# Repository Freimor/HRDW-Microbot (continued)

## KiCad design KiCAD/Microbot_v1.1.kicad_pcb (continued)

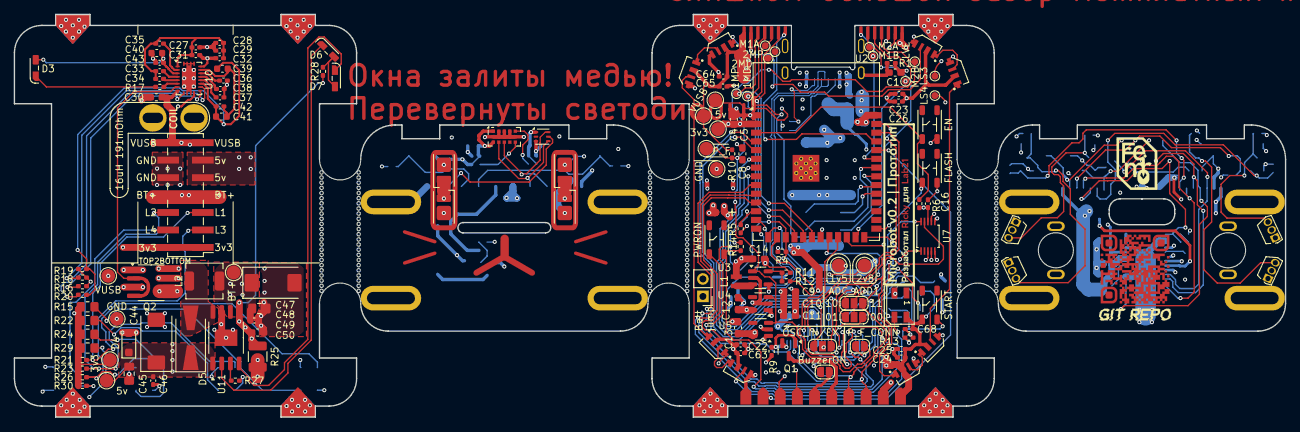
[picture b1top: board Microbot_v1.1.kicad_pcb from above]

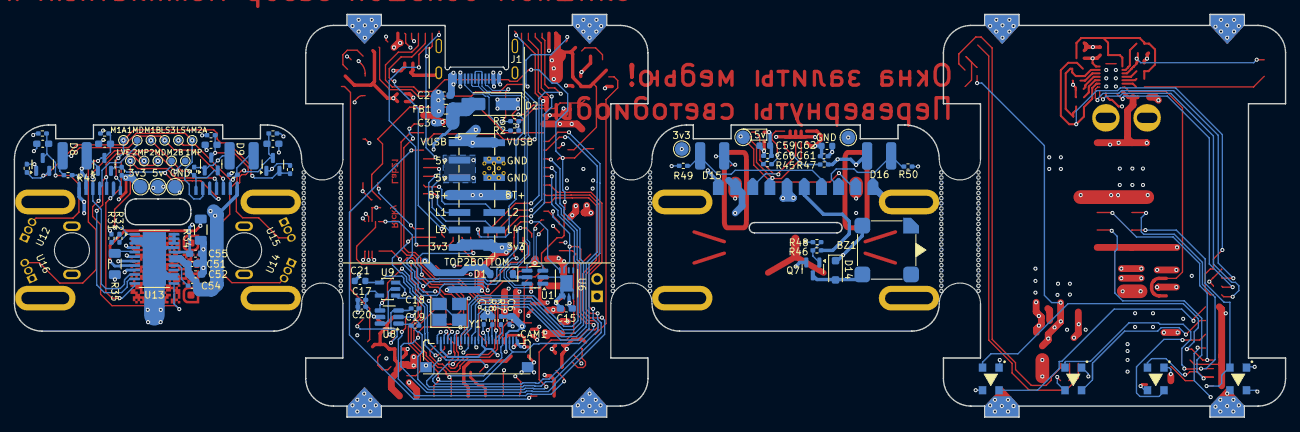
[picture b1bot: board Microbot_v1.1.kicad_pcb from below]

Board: 4 copper layers, 185.0 x 58.6 mm, 246 parts (92 on the bottom side), 123 nets.

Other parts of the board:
Ref**: Val**; Graphic

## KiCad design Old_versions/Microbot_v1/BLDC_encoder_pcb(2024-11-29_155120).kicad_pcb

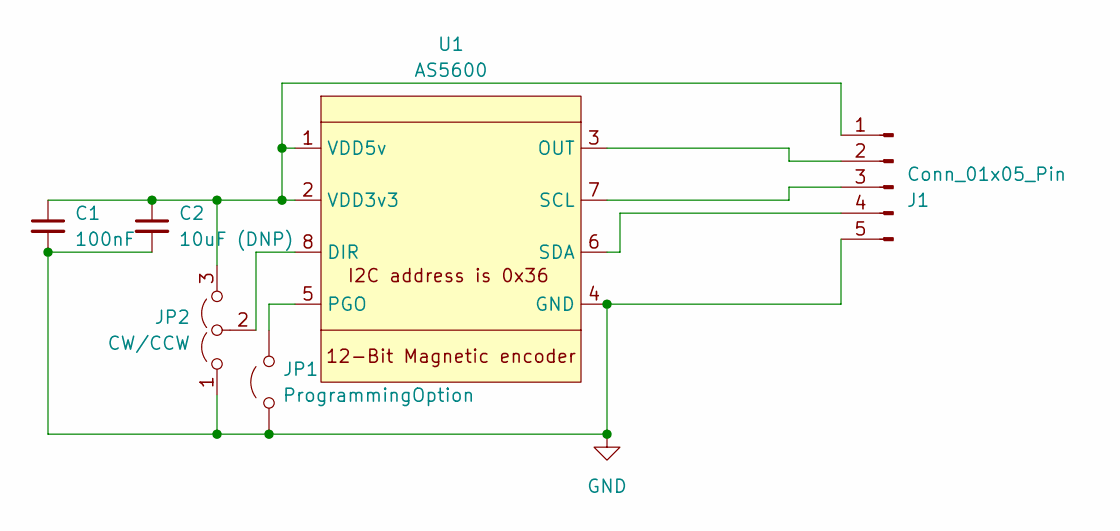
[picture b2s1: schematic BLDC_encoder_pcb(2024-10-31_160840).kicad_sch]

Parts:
C1: 100nF; C_0402_1005Metric_Pad0.74x0.62mm_HandSolder
C2: 10uF (DNP); C_0603_1608Metric_Pad1.08x0.95mm_HandSolder
J1: Conn_01x05_Pin; Microbot_BLDC_encoder
JP1: ProgrammingOption; SolderJumper-2_P1.3mm_Open_RoundedPad1.0x1.5mm
JP2: CW/CCW; SolderJumper-3_P1.3mm_Open_RoundedPad1.0x1.5mm_NumberLabels
U1: AS5600; SOIC-8_3.9x4.9mm_P1.27mm

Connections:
GND: C1.2, C2.2, J1.5, JP1.1 (A), JP2.1 (A), U1.4 (GND)
unnamed: C1.1, C2.1, J1.1, JP2.3 (B), U1.1 (VDD5v), U1.2 (VDD3v3)
unnamed: J1.2, U1.3 (OUT)
unnamed: J1.3, U1.7 (SCL)
unnamed: J1.4, U1.6 (SDA)
unnamed: JP1.2 (B), U1.5 (PGO)
unnamed: JP2.2 (C), U1.8 (DIR)

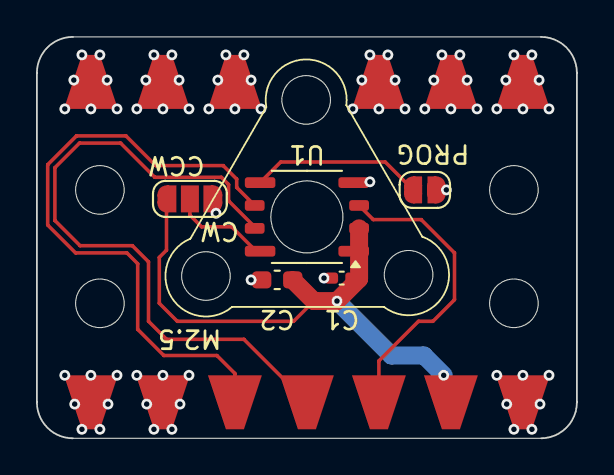
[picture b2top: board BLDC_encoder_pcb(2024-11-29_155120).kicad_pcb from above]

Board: 2 copper layers, 30.0 x 22.3 mm, 6 parts (0 on the bottom side), 7 nets.

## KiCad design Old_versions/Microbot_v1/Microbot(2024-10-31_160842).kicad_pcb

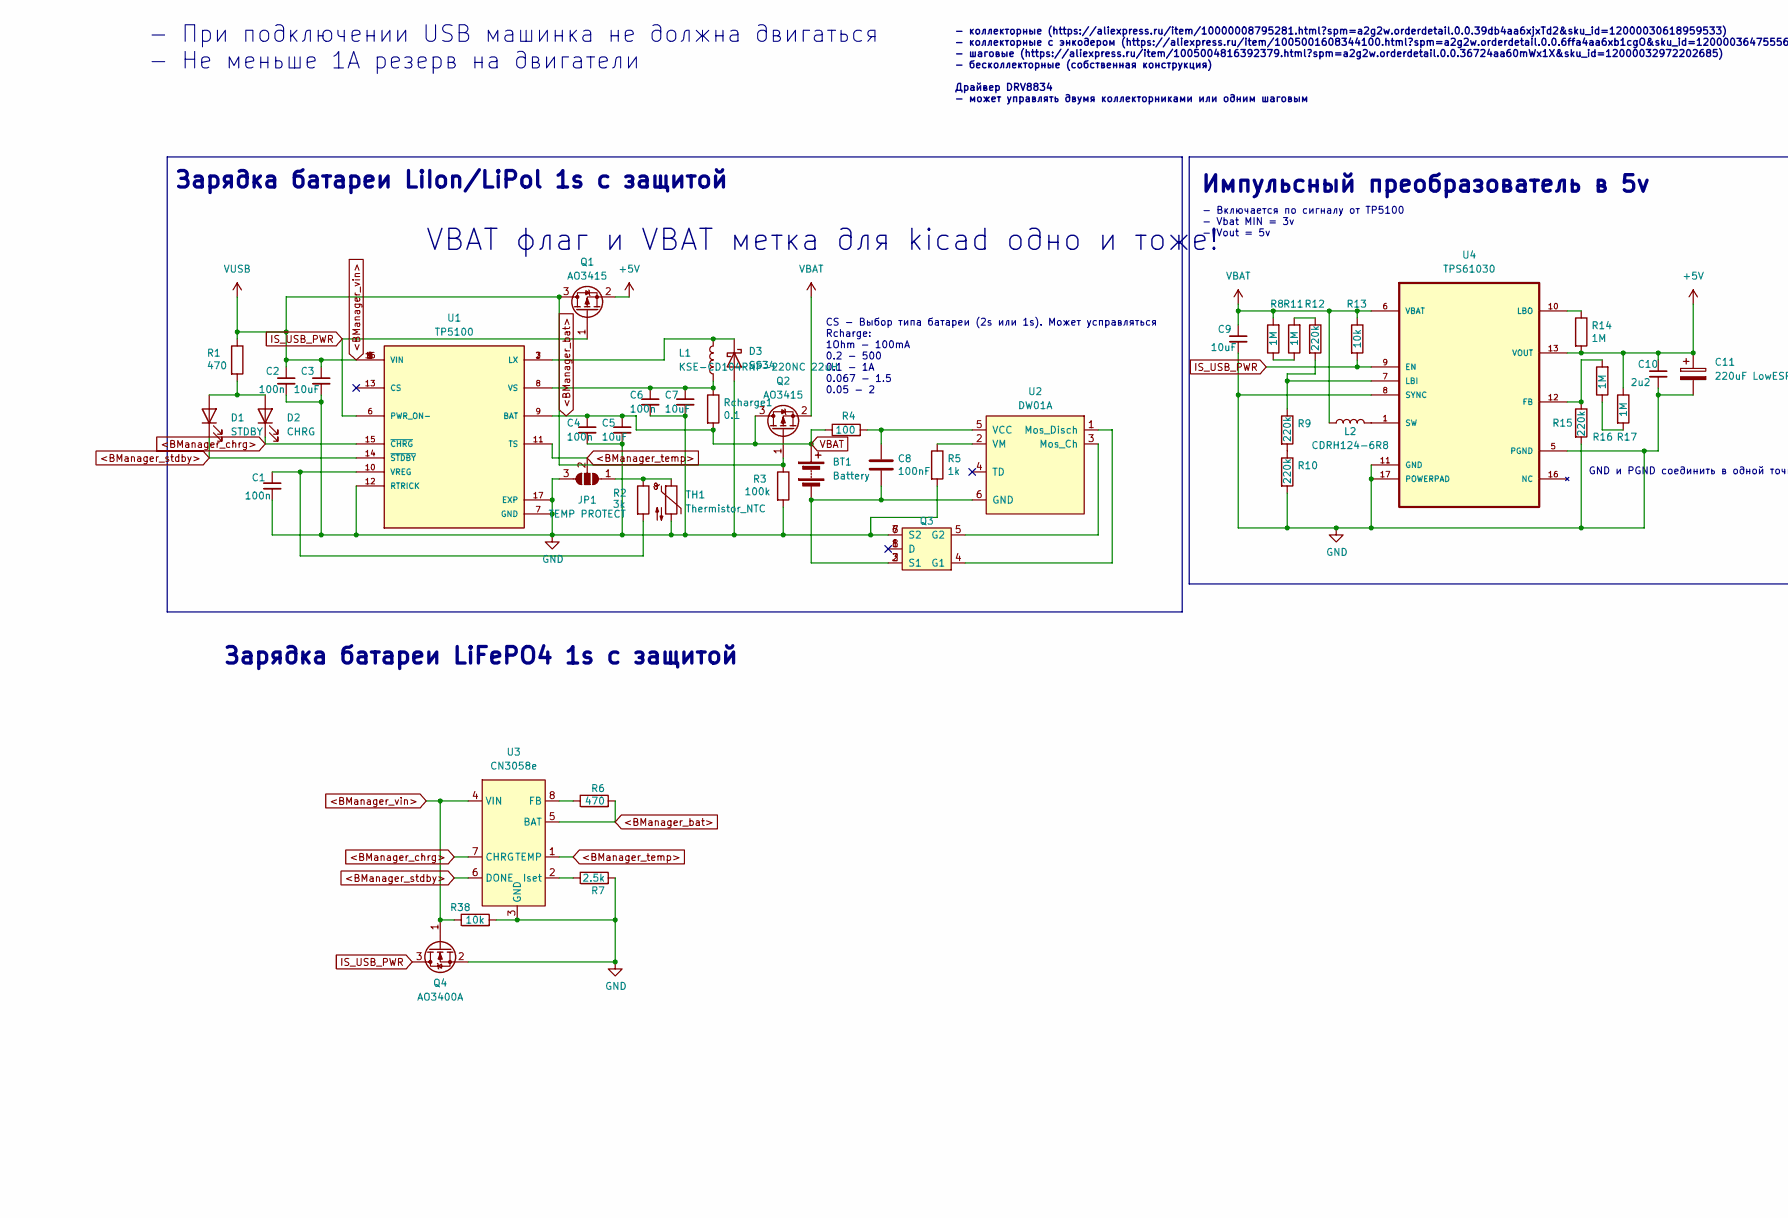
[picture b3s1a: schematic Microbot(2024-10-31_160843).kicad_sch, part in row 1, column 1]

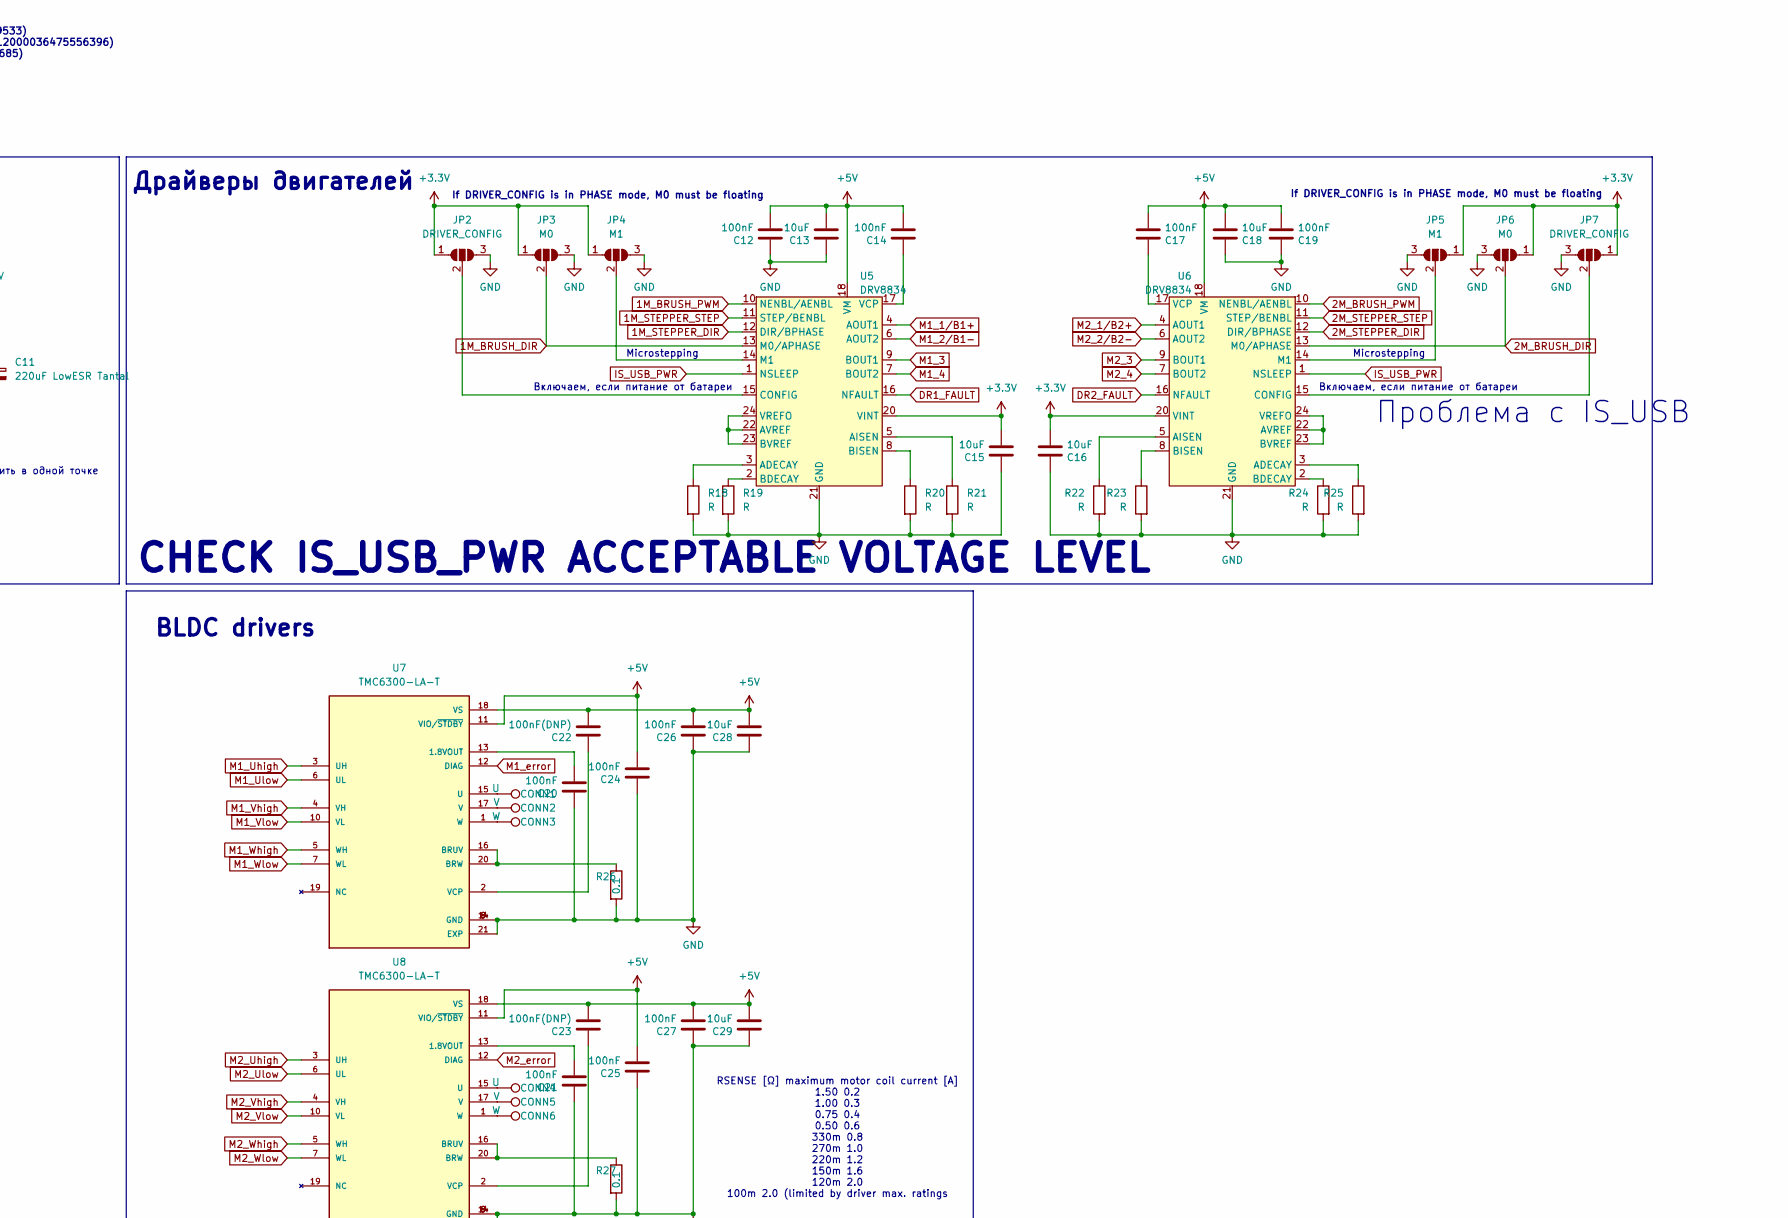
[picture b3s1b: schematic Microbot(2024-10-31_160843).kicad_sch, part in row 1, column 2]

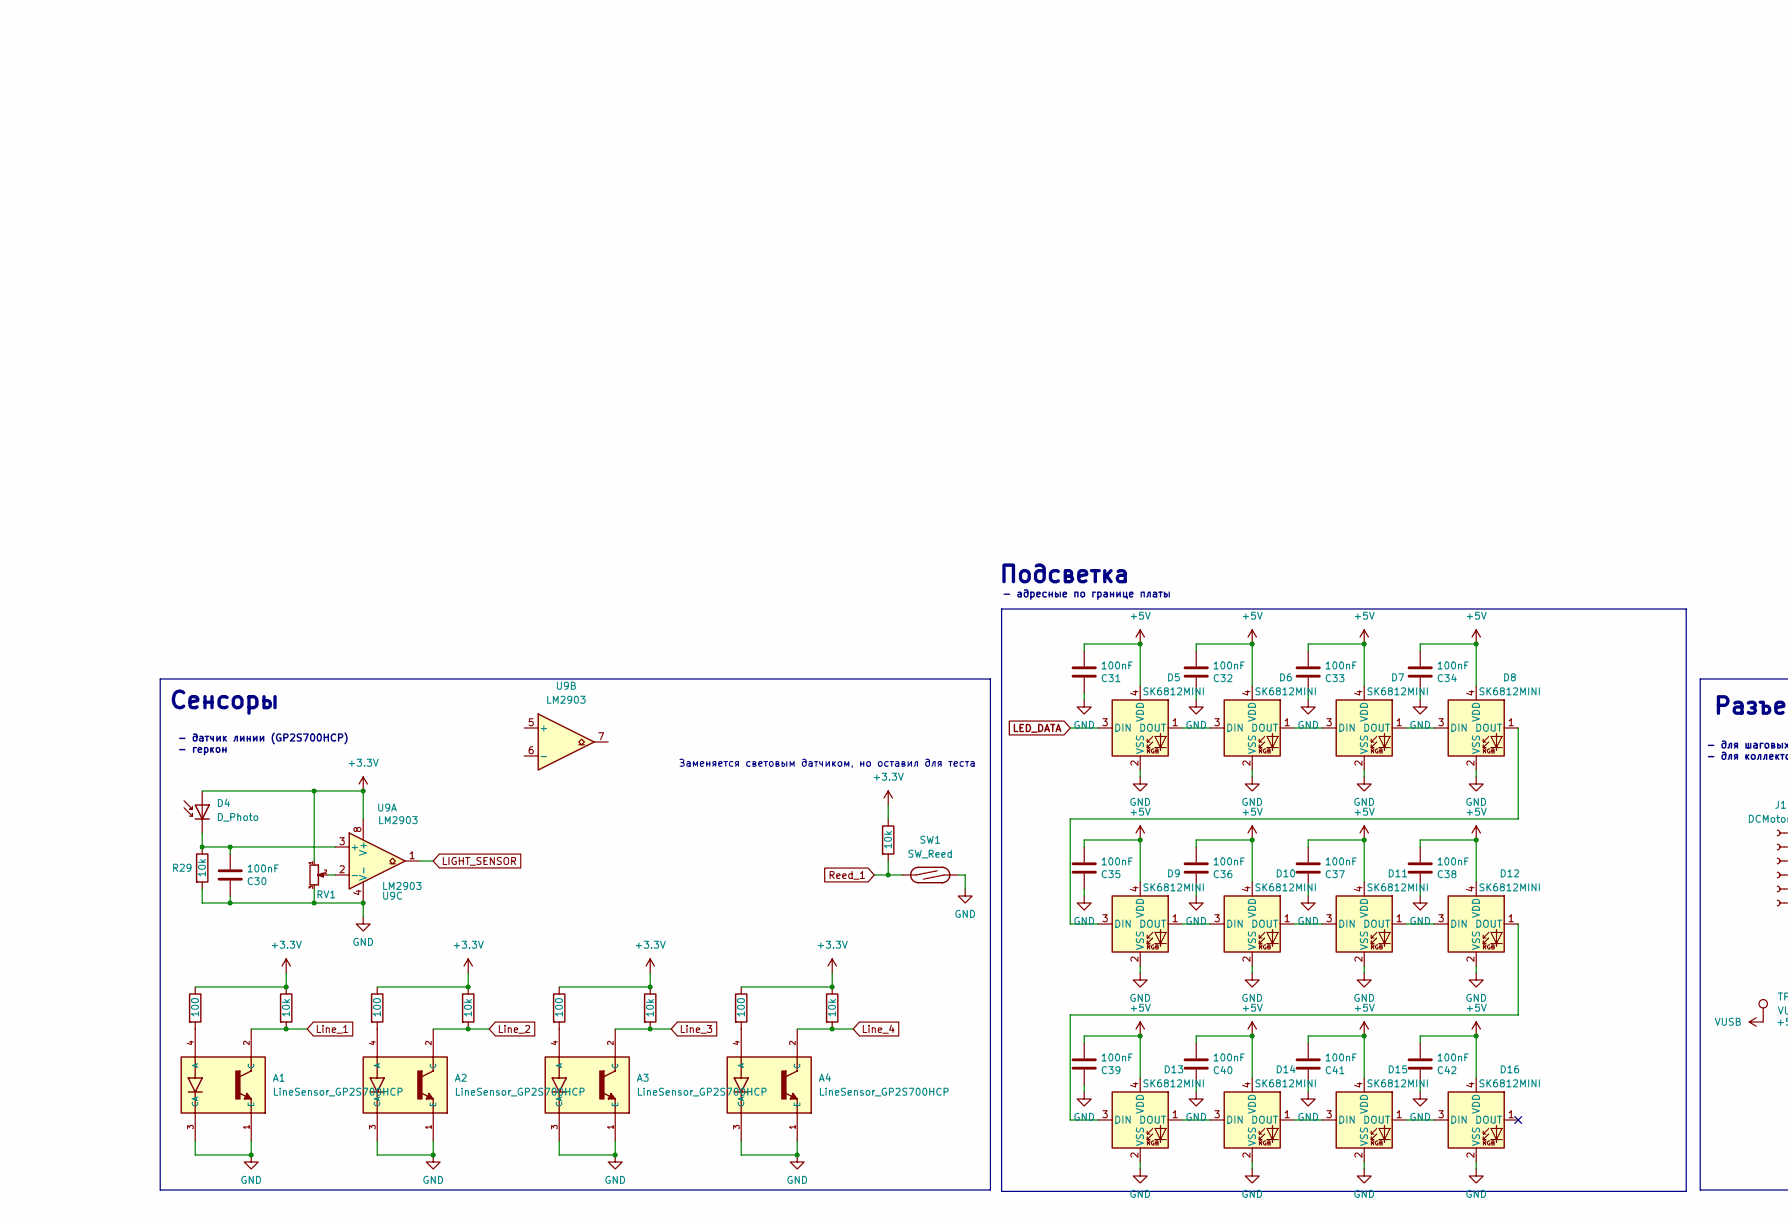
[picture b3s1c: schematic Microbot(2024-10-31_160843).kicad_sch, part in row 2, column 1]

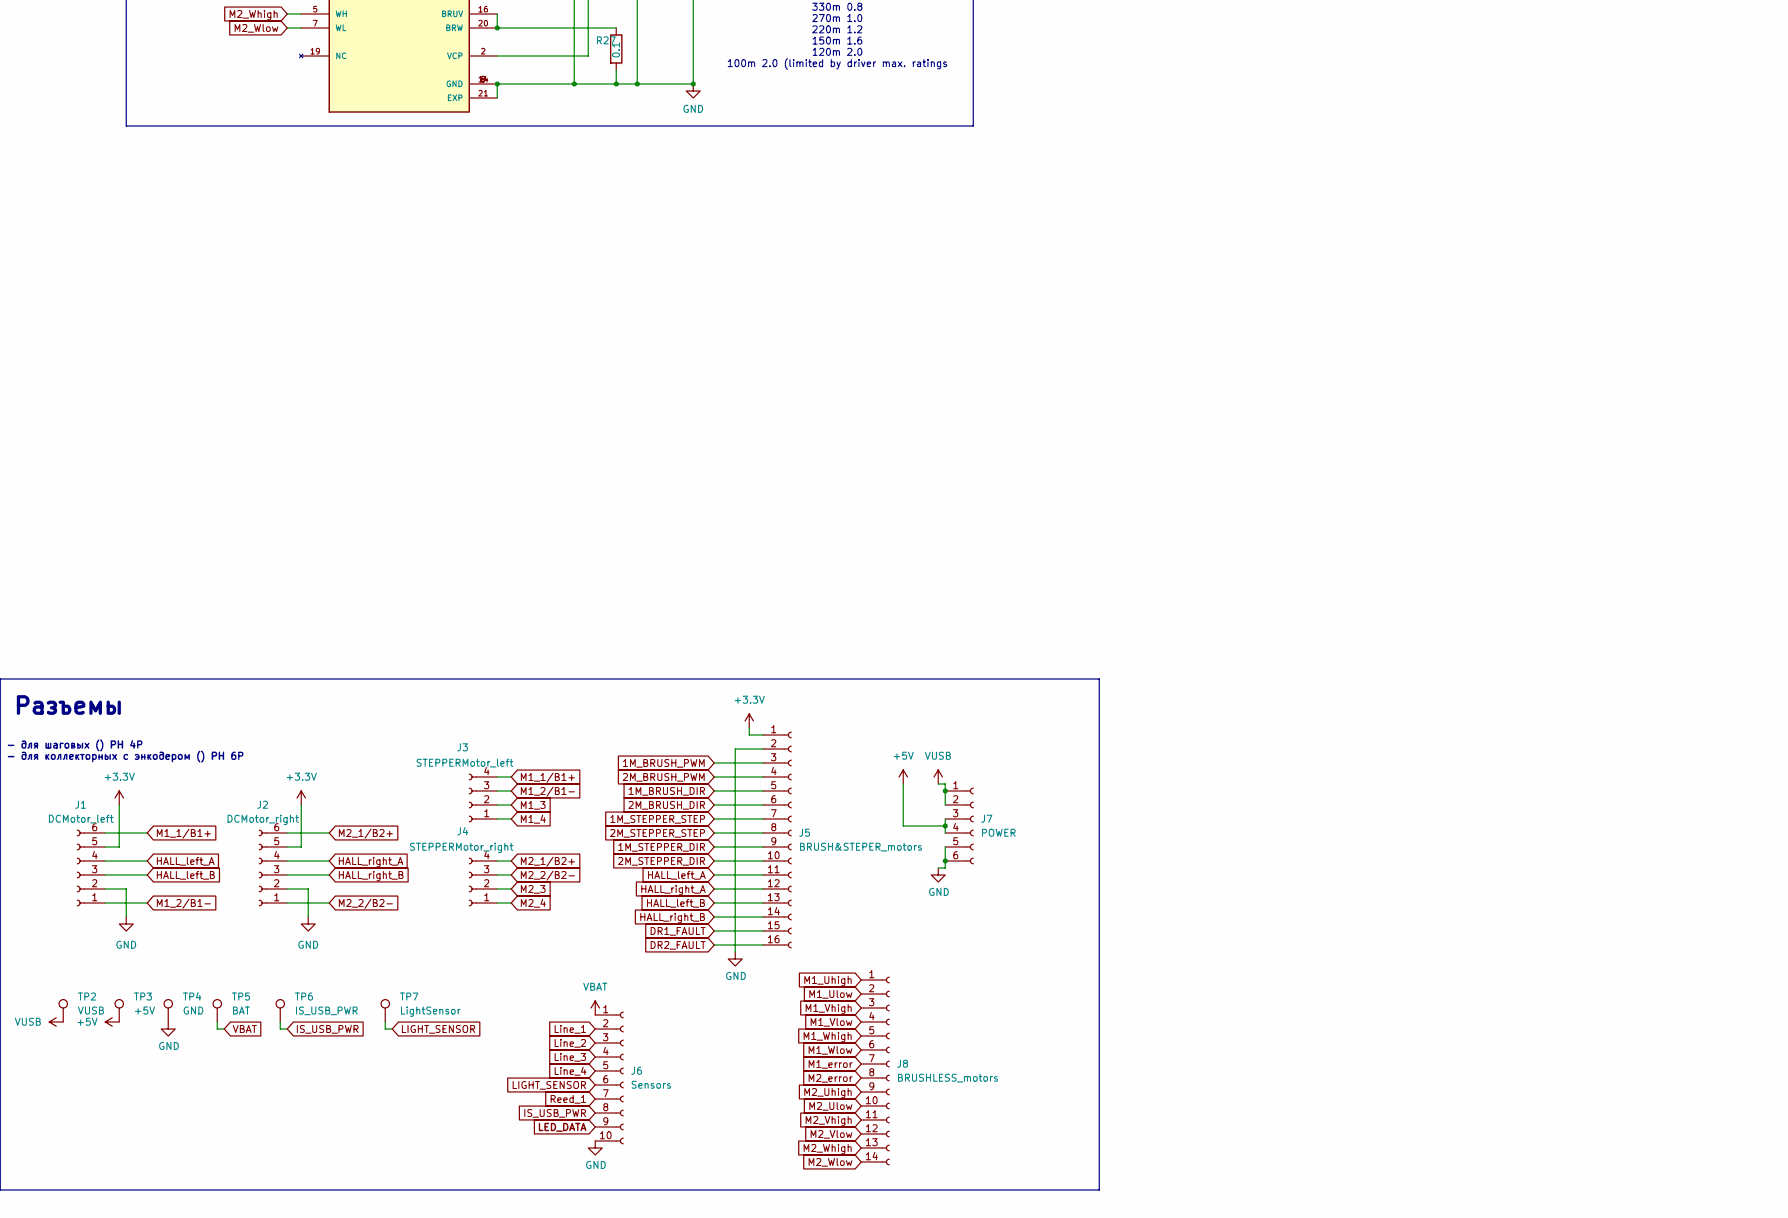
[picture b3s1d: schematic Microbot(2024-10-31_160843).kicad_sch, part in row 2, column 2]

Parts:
A1, A2, A3, A4: LineSensor_GP2S700HCP; GP2S700HCP; PARTREV Oct. 3. 2005
BT1: Battery; Conn_BAT_18650_LowProfile
C1, C2, C4, C6: 100n; C_0402_1005Metric_Pad0.74x0.62mm_HandSolder
C3, C5, C7, C9, C13, C15, C16, C18, C28, C29: 10uF; C_0603_1608Metric_Pad1.08x0.95mm_HandSolder
C8, C12, C14, C17, C19, C20, C21, C24, C25, C26, C27, C30, C31, C32, C33, C34, C35, C36, C37, C38, C39, C40, C41, C42: 100nF; C_0402_1005Metric_Pad0.74x0.62mm_HandSolder
C10: 2u2; C_0603_1608Metric_Pad1.08x0.95mm_HandSolder
C11: 220uF LowESR Tantal; CP_EIA-7343-31_Kemet-D
C22, C23: 100nF(DNP); C_0402_1005Metric_Pad0.74x0.62mm_HandSolder
CONN1, CONN4: U; TestPoint_Pad_D1.5mm
CONN2, CONN5: V; TestPoint_Pad_D1.5mm
CONN3, CONN6: W; TestPoint_Pad_D1.5mm
D1: STDBY; LED_0603_1608Metric
D2: CHRG; LED_0603_1608Metric
D3: SS34; D_SMA-SMB_Universal_Handsoldering
D4: D_Photo; R_LDR_5.1x4.3mm_P3.4mm_Vertical
D5, D6, D7, D8, D9, D10, D11, D12, D13, D14, D15, D16: SK6812MINI; LED_SK6812MINI_PLCC4_3.5x3.5mm_P1.75mm
J1: DCMotor_left; JST_ZH_B6B-ZR-SM4-TF_1x06-1MP_P1.50mm_Vertical
J2: DCMotor_right; JST_ZH_B6B-ZR-SM4-TF_1x06-1MP_P1.50mm_Vertical
J3: STEPPERMotor_left; JST_PH_S4B-PH-SM4-TB_1x04-1MP_P2.00mm_Horizontal
J4: STEPPERMotor_right; JST_PH_S4B-PH-SM4-TB_1x04-1MP_P2.00mm_Horizontal
J5: BRUSH&STEPER_motors; PinHeader_2x08_P2.54mm_Vertical_SMD
J6: Sensors; PinHeader_2x05_P2.54mm_Vertical_SMD
J7: POWER; PinHeader_2x03_P2.54mm_Vertical_SMD
J8: BRUSHLESS_motors; PinHeader_2x07_P2.54mm_Vertical_SMD
JP1: TEMP PROTECT; SolderJumper-3_P1.3mm_Open_RoundedPad1.0x1.5mm
JP2, JP7: DRIVER_CONFIG; SolderJumper-3_P1.3mm_Open_RoundedPad1.0x1.5mm
JP3, JP6: M0; SolderJumper-3_P1.3mm_Open_RoundedPad1.0x1.5mm
JP4, JP5: M1; SolderJumper-3_P1.3mm_Open_RoundedPad1.0x1.5mm
L1: KSE-CD104RNP-220NC 22uH; L_10.4x10.4_H4.8
L2: CDRH124-6R8; L_12x12mm_H4.5mm
Q1, Q2: AO3415; SOT-23
Q3: 8205(Dual_Mosfet); SOT-23-6
Q4: AO3400A; SOT-23
R1, R6: 470; R_0402_1005Metric_Pad0.72x0.64mm_HandSolder
R2: 3k; R_0603_1608Metric
R3: 100k; R_0402_1005Metric_Pad0.72x0.64mm_HandSolder
R4: 100; R_0402_1005Metric_Pad0.72x0.64mm_HandSolder
R5: 1k; R_0402_1005Metric_Pad0.72x0.64mm_HandSolder
R7: 2.5k; R_0805_2012Metric_Pad1.20x1.40mm_HandSolder
R8, R11, R14, R16, R17: 1M; R_0402_1005Metric_Pad0.72x0.64mm_HandSolder
R9, R10, R12, R15: 220k; R_0402_1005Metric_Pad0.72x0.64mm_HandSolder
R13, R29, R30, R32, R34, R36, R37, R38: 10k; R_0402_1005Metric_Pad0.72x0.64mm_HandSolder
R18, R19, R20, R21, R22, R23, R24, R25: R; R_0805_2012Metric_Pad1.20x1.40mm_HandSolder
R26, R27: 0.1; R_0805_2012Metric_Pad1.20x1.40mm_HandSolder
R28, R31, R33, R35: 100; R_0805_2012Metric_Pad1.20x1.40mm_HandSolder
RV1: R_Potentiometer_Small; POT_SMD_3x3mm
Rcharge1: 0.1; R_1206_3216Metric_Pad1.30x1.75mm_HandSolder
SW1: SW_Reed; Reed_MKA10110
TH1: Thermistor_NTC; R_Axial_DIN0204_L3.6mm_D1.6mm_P7.62mm_Horizontal
TP2: VUSB; TestPoint_Pad_D2.0mm
TP3: +5V; TestPoint_Pad_D2.0mm
TP4: GND; TestPoint_Pad_D2.0mm
TP5: BAT; TestPoint_Pad_D2.0mm
TP6: IS_USB_PWR; TestPoint_Pad_D2.0mm
TP7: LightSensor; TestPoint_Pad_D2.0mm
U1: TP5100; QFN-16-1EP_4x4mm_P0.65mm_EP2.1x2.1mm; PARTREV 2.3
U2: DW01A; SOT-23-6_Handsoldering
U3: CN3058e; SOP-8_3.9x4.9mm_P1.27mm
U4: TPS61030; HTSSOP-16-1EP_4.4x5mm_P0.65mm_EP3x3mm; MPN TPS61030
U5, U6: DRV8834; HTSSOP-24-1EP_4.4x7.8mm_P0.65mm_EP3.4x7.8mm_Mask2.4x2.98mm
U7, U8: TMC6300-LA-T; TMC6300; PARTREV 1.08
U9: LM2903; SOIC-8_3.9x4.9mm_P1.27mm

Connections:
1M_BRUSH_DIR: J5.5, JP3.2 (C), U5.13 (M0/APHASE)
1M_BRUSH_PWM: J5.3, U5.10 (NENBL/AENBL)
1M_STEPPER_DIR: J5.9, U5.12 (DIR/BPHASE)
1M_STEPPER_STEP: J5.7, U5.11 (STEP/BENBL)
2M_BRUSH_DIR: J5.6, JP6.2 (C), U6.13 (M0/APHASE)
2M_BRUSH_PWM: J5.4, U6.10 (NENBL/AENBL)
2M_STEPPER_DIR: J5.10, U6.12 (DIR/BPHASE)
2M_STEPPER_STEP: J5.8, U6.11 (STEP/BENBL)
+3.3V: C15.2, C16.2, D4.2 (A), J1.5, J2.5, J5.1, JP2.1 (A), JP3.1 (A), JP4.1 (A), JP5.1 (A), JP6.1 (A), JP7.1 (A), R28.1, R30.1, R31.1, R32.1, R33.1, R34.1, R35.1, R36.1, R37.1, RV1.1, U5.20 (VINT), U6.20 (VINT), U9.8 (V+)
+5V: C10.1, C11.1, C12.2, C13.2, C14.2, C17.2, C18.2, C19.2, C22.2, C23.2, C24.2, C25.2, C26.2, C27.2, C28.2, C29.2, C31.2, C32.2, C33.2, C34.2, C35.2, C36.2, C37.2, C38.2, C39.2, C40.2, C41.2, C42.2, D5.4 (VDD), D6.4 (VDD), D7.4 (VDD), D8.4 (VDD), D9.4 (VDD), D10.4 (VDD), D11.4 (VDD), D12.4 (VDD), D13.4 (VDD), D14.4 (VDD), D15.4 (VDD), D16.4 (VDD), J7.3, J7.4, Q1.2 (S), R14.2, R17.1, TP3.1, U4.13 (VOUT), U4.14 (VOUT_2), U4.15 (VOUT_3), U5.18 (VM), U5.19 (VM), U6.18 (VM), U6.19 (VM), U7.11 (VIO/~STDBY), U7.18 (VS), U8.11 (VIO/~STDBY), U8.18 (VS)
<BManager_bat>: BT1.1 (+), C4.1, C5.1, C9.1, J6.1, L2.1, Q2.2 (S), Q2.3 (D), R4.1, R6.2, R8.2, R13.1, Rcharge1.2, TP5.1, U1.9 (BAT), U3.5 (BAT), U4.6 (VBAT)
<BManager_chrg>: D2.1 (K), U1.15 (~CHRG), U3.7 (CHRG)
<BManager_stdby>: D1.1 (K), U1.14 (~STDBY), U3.6 (DONE)
<BManager_temp>: JP1.2 (C), U1.11 (TS), U3.1 (TEMP)
<BManager_vin>: C2.1, C3.1, J7.1, J7.2, Q1.3 (D), Q2.1 (G), Q4.1 (G), R1.1, R3.1, R38.1, TP2.1, U1.1 (VIN), U1.4 (VIN), U1.5 (VIN), U1.16 (VIN), U3.4 (VIN)
DR1_FAULT: J5.15, U5.16 (NFAULT)
DR2_FAULT: J5.16, U6.16 (NFAULT)
GND: A1.1 (E), A1.3 (CA), A2.1 (E), A2.3 (CA), A3.1 (E), A3.3 (CA), A4.1 (E), A4.3 (CA), C1.2, C2.2, C3.2, C4.2, C5.2, C6.2, C7.2, C9.2, C10.2, C11.2, C12.1, C13.1, C15.1, C16.1, C18.1, C19.1, C20.1, C21.1, C24.1, C25.1, C26.1, C27.1, C28.1, C29.1, C30.1, C31.1, C32.1, C33.1, C34.1, C35.1, C36.1, C37.1, C38.1, C39.1, C40.1, C41.1, C42.1, D3.2 (A), D5.2 (VSS), D6.2 (VSS), D7.2 (VSS), D8.2 (VSS), D9.2 (VSS), D10.2 (VSS), D11.2 (VSS), D12.2 (VSS), D13.2 (VSS), D14.2 (VSS), D15.2 (VSS), D16.2 (VSS), J1.2, J2.2, J5.2, J6.10, J7.5, J7.6, JP1.3 (B), JP2.3 (B), JP3.3 (B), JP4.3 (B), JP5.3 (B), JP6.3 (B), JP7.3 (B), Q3.6 (S2), Q3.7 (S2), Q4.2 (S), R3.2, R5.2, R7.2, R10.2, R15.2, R18.2, R19.2, R20.2, R21.2, R22.2, R23.2, R24.2, R25.2, R26.2, R27.2, R29.2, R38.2, RV1.3, SW1.2, TH1.2, TP4.1, U1.7 (GND), U1.12 (RTRICK), U1.17 (EXP), U3.3 (GND), U4.3 (PGND_2), U4.4 (PGND_3), U4.5 (PGND), U4.8 (SYNC), U4.11 (GND), U4.17 (POWERPAD), U5.21 (GND), U6.21 (GND), U7.8 (GND), U7.9 (GND), U7.14 (GND), U7.21 (EXP), U8.8 (GND), U8.9 (GND), U8.14 (GND), U8.21 (EXP), U9.4 (V-)
HALL_left_A: J1.4, J5.11
HALL_left_B: J1.3, J5.13
HALL_right_A: J2.4, J5.12
HALL_right_B: J2.3, J5.14
IS_USB_PWR: J6.8, Q1.1 (G), Q4.3 (D), R13.2, TP6.1, U1.6 (PWR_ON-), U4.9 (EN), U5.1 (NSLEEP), U6.1 (NSLEEP)
LED_DATA: D5.3 (DIN), J6.9
Line_1: A1.2 (C), J6.2, R30.2
Line_2: A2.2 (C), J6.3, R32.2
Line_3: A3.2 (C), J6.4, R34.2
Line_4: A4.2 (C), J6.5, R36.2
M1_1/B1+: J1.6, J3.4, U5.4 (AOUT1)
M1_2/B1-: J1.1, J3.3, U5.6 (AOUT2)
M1_3: J3.2, U5.9 (BOUT1)
M1_4: J3.1, U5.7 (BOUT2)
M1_Uhigh: J8.1, U7.3 (UH)
M1_Ulow: J8.2, U7.6 (UL)
M1_Vhigh: J8.3, U7.4 (VH)
M1_Vlow: J8.4, U7.10 (VL)
M1_Whigh: J8.5, U7.5 (WH)
M1_Wlow: J8.6, U7.7 (WL)
M1_error: J8.7, U7.12 (DIAG)
M2_1/B2+: J2.6, J4.4, U6.4 (AOUT1)
M2_2/B2-: J2.1, J4.3, U6.6 (AOUT2)
M2_3: J4.2, U6.9 (BOUT1)
M2_4: J4.1, U6.7 (BOUT2)
M2_Uhigh: J8.9, U8.3 (UH)
M2_Ulow: J8.10, U8.6 (UL)
M2_Vhigh: J8.11, U8.4 (VH)
M2_Vlow: J8.12, U8.10 (VL)
M2_Whigh: J8.13, U8.5 (WH)
M2_Wlow: J8.14, U8.7 (WL)
M2_error: J8.8, U8.12 (DIAG)
unnamed: A1.4 (A), R28.2
unnamed: A2.4 (A), R31.2
unnamed: A3.4 (A), R33.2
unnamed: A4.4 (A), R35.2
unnamed: BT1.2 (-), C8.2, Q3.2 (S1), Q3.3 (S1), U2.6 (GND)
unnamed: D1.2 (A), D2.2 (A), R1.2
unnamed: D3.1 (K), L1.2, U1.2 (LX), U1.3 (LX)
unnamed: C30.2, D4.1 (K), R29.1, U9.3 (+)
unnamed: D5.1 (DOUT), D6.3 (DIN)
unnamed: D6.1 (DOUT), D7.3 (DIN)
unnamed: D7.1 (DOUT), D8.3 (DIN)
unnamed: D8.1 (DOUT), D9.3 (DIN)
unnamed: D9.1 (DOUT), D10.3 (DIN)
unnamed: D10.1 (DOUT), D11.3 (DIN)
unnamed: D11.1 (DOUT), D12.3 (DIN)
unnamed: D12.1 (DOUT), D13.3 (DIN)
unnamed: D13.1 (DOUT), D14.3 (DIN)
unnamed: D14.1 (DOUT), D15.3 (DIN)
unnamed: D15.1 (DOUT), D16.3 (DIN)
unnamed: JP1.1 (A), R2.1, TH1.1
unnamed: JP2.2 (C), U5.15 (CONFIG)
unnamed: JP4.2 (C), U5.14 (M1)
unnamed: JP5.2 (C), U6.14 (M1)
unnamed: JP7.2 (C), U6.15 (CONFIG)
unnamed: L2.2, U4.1 (SW), U4.2 (SW)
unnamed: Q3.4 (G1), U2.1 (Mos_Disch)
unnamed: Q3.5 (G2), U2.3 (Mos_Ch)
unnamed: R9.2, R10.1
unnamed: R8.1, R11.1
unnamed: R11.2, R12.1
unnamed: R16.1, R17.2
unnamed: C1.1, R2.2, U1.10 (VREG)
unnamed: C6.1, C7.1, L1.1, Rcharge1.1, U1.8 (VS)
unnamed: C8.1, R4.2, U2.5 (VCC)
unnamed: R5.1, U2.2 (VM)
unnamed: R6.1, U3.8 (FB)
unnamed: R7.1, U3.2 (Iset)
unnamed: R15.1, R16.2, U4.12 (FB)
unnamed: R9.1, R12.2, U4.7 (LBI)
unnamed: R14.1, U4.10 (LBO)
unnamed: R18.1, U5.3 (ADECAY)
unnamed: R21.1, U5.5 (AISEN)
unnamed: U5.22 (AVREF), U5.23 (BVREF), U5.24 (VREFO)
unnamed: R19.1, U5.2 (BDECAY)
unnamed: R20.1, U5.8 (BISEN)
unnamed: C14.1, U5.17 (VCP)
unnamed: R25.1, U6.3 (ADECAY)
unnamed: R22.1, U6.5 (AISEN)
unnamed: U6.22 (AVREF), U6.23 (BVREF), U6.24 (VREFO)
unnamed: R24.1, U6.2 (BDECAY)
unnamed: R23.1, U6.8 (BISEN)
unnamed: C17.1, U6.17 (VCP)
unnamed: C20.2, U7.13 (1.8VOUT)
unnamed: R26.1, U7.16 (BRUV), U7.20 (BRW)
unnamed: CONN1.1, U7.15 (U)
unnamed: CONN2.1, U7.17 (V)
unnamed: C22.1, U7.2 (VCP)
unnamed: CONN3.1, U7.1 (W)
unnamed: C21.2, U8.13 (1.8VOUT)
unnamed: R27.1, U8.16 (BRUV), U8.20 (BRW)
unnamed: CONN4.1, U8.15 (U)
unnamed: CONN5.1, U8.17 (V)
unnamed: C23.1, U8.2 (VCP)
unnamed: CONN6.1, U8.1 (W)
unnamed: RV1.2, U9.2 (-)

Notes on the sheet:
Импульсный преобразователь в 5v
Включаем, если питание от батареи
- для шаговых () PH 4P - для коллекторных с энкодером () PH 6P
Заменяется световым датчиком, но оставил для теста
Драйверы двигателей
- При подключении USB машинка не должна двигаться - Не меньше 1А резерв на двигатели
Разъемы
Зарядка батареи LiFePO4 1s с защитой
- Включается по сигналу от TP5100 - Vbat MIN = 3v - Vout = 5v
Проблема с IS_USB
If DRIVER_CONFIG is in PHASE mode, M0 must be floating
- адресные по границе платы
Подсветка
Зарядка батареи LiIon/LiPol 1s с защитой
- коллекторные (https://aliexpress.ru/item/10000008795281.html?spm=a2g2w.orderdetail.0.0.39db4aa6xjxTd2&sku_id=12000030618959533) - коллекторные с энкодером (https://aliexpress.ru/item/1005001608344100.html?spm=a2g2w.orderdetail.0.0.6ffa4aa6xb1cgO&sku_id=12000036475556396) - шаговые (https://aliexp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
CHECK IS_USB_PWR ACCEPTABLE VOLTAGE LEVEL
- датчик линии (GP2S700HCP) - геркон
Сенсоры
Microstepping
VBAT флаг и VBAT метка для kicad одно и тоже!
CS - Выбор типа батареи (2s или 1s). Может усправляться Rcharge: 1Ohm - 100mA 0.2 - 500 0.1 - 1A 0.067 - 1.5 0.05 - 2
GND и PGND соединить в одной точке
RSENSE [Ω] maximum motor coil current [A] 1.50 0.2 1.00 0.3 0.75 0.4 0.50 0.6 330m 0.8 270m 1.0 220m 1.2 150m 1.6 120m 2.0 100m 2.0 (limited by driver max. ratings
BLDC drivers

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
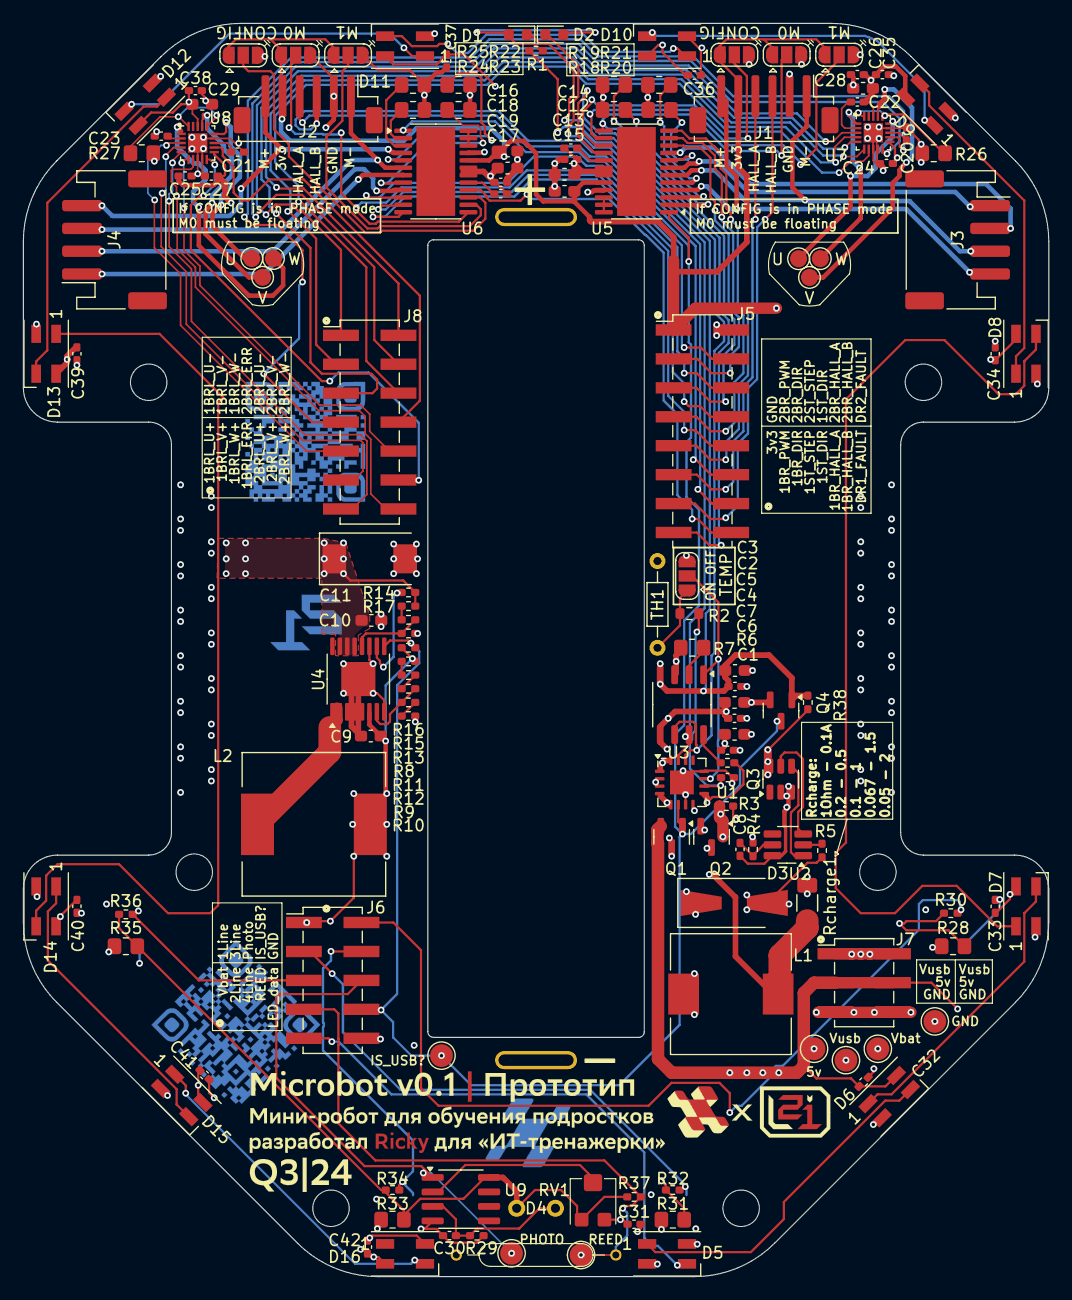
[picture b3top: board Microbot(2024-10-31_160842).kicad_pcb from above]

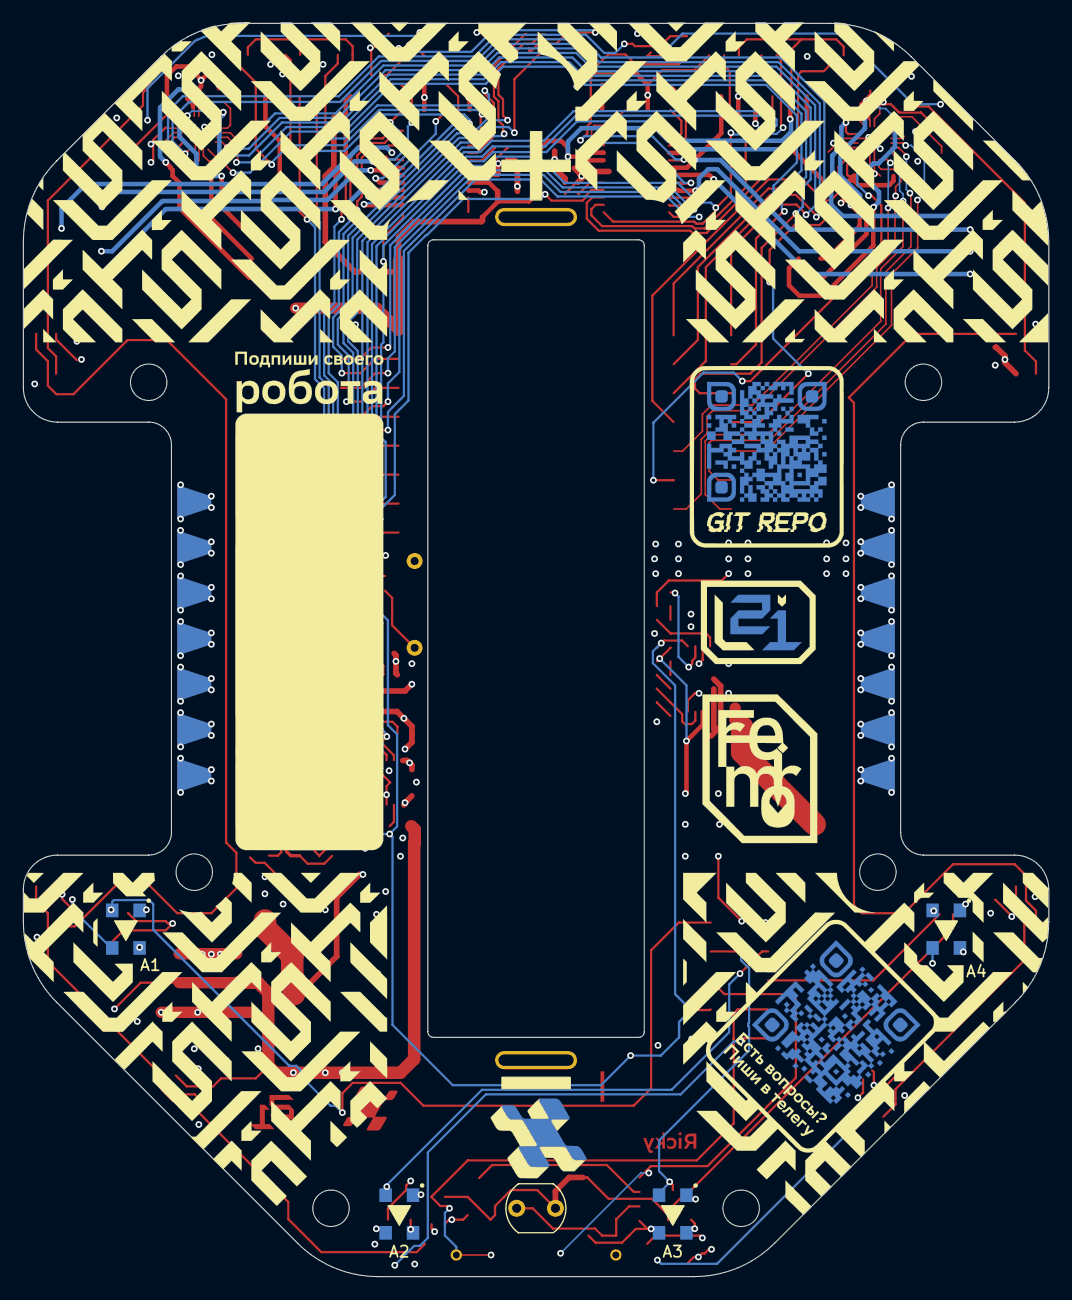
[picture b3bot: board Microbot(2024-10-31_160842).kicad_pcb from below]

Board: 4 copper layers, 90.0 x 110.0 mm, 150 parts (5 on the bottom side), 117 nets.

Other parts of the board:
Ref**: Val**; Microbot_Silk_TOP_1
Ref**#2: Val**; Microbot_Silk_BOTTOM
TP7#2: LightSensor; TestPoint_Pad_D2.0mm

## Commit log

2026-04-04 Initial commit of comprehensive robot library for ESP32S3-N16R8 platform with full hardware integration support
    - robot_library.cpp: Core implementation with initialization and control functions for all hardware components including battery monitoring (LC709203), photoresistors via ADS1015, line sensors (GP257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
    - robot_config.h: Hardware pin definitions and configuration constants for all connected peripherals
    - basic_example.ino: Complete usage example demonstrating sensor reading, motor control, LED effects, and obstacle detection
    - .gitignore: P
2026-04-04 update branch
2026-04-04 Fix robot_config.h
